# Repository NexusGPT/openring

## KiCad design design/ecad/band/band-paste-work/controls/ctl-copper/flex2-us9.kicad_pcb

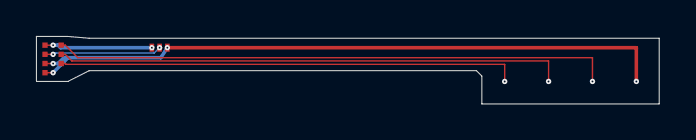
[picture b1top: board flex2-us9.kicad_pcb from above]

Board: 2 copper layers, 34.6 x 3.8 mm, 6 parts (0 on the bottom side), 6 nets.

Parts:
CP1, CP2, CP3, CP4: CP_Pad_1.6
J_BAND_B: J_BAND_B_TAIL
PRT1: PRT1_Tabs

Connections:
GND: CP4.1, J_BAND_B.2, J_BAND_B.7, PRT1.2
NTC: J_BAND_B.3, PRT1.3
USB_DN: CP2.1, J_BAND_B.5
USB_DP: CP3.1, J_BAND_B.6
VBAT: J_BAND_B.1, PRT1.1
VBUS: CP1.1, J_BAND_B.4

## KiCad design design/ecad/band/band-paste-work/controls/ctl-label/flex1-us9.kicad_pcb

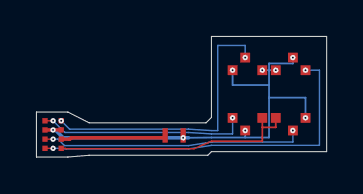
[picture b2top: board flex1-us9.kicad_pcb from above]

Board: 2 copper layers, 16.1 x 6.7 mm, 7 parts (0 on the bottom side), 7 nets.

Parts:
J_BAND_A: J_BAND_A_TAIL
M1: W0525AB001D_Lands
SW1, SW3, SW4, SW5: Alps_SKTAAAE010_pads34
SW2: Alps_SKTAAAE010_4pad

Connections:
BTN_REC: J_BAND_A.5, SW2.1, SW2.3
GND: J_BAND_A.6, J_BAND_A.8, M1.2, SW1.4, SW2.2, SW2.4, SW3.4, SW4.4, SW5.4
JOY_DOWN: J_BAND_A.2, SW3.3
JOY_LEFT: J_BAND_A.3, SW4.3
JOY_RIGHT: J_BAND_A.4, SW5.3
JOY_UP: J_BAND_A.1, SW1.3
VMOT: J_BAND_A.7, M1.1
